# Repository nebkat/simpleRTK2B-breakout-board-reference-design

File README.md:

# ArduSimple simpleRTK2B Breakout Board

This repository contains KiCAD schematics and the PCB design for a breakout board for the simpleRTK2B.

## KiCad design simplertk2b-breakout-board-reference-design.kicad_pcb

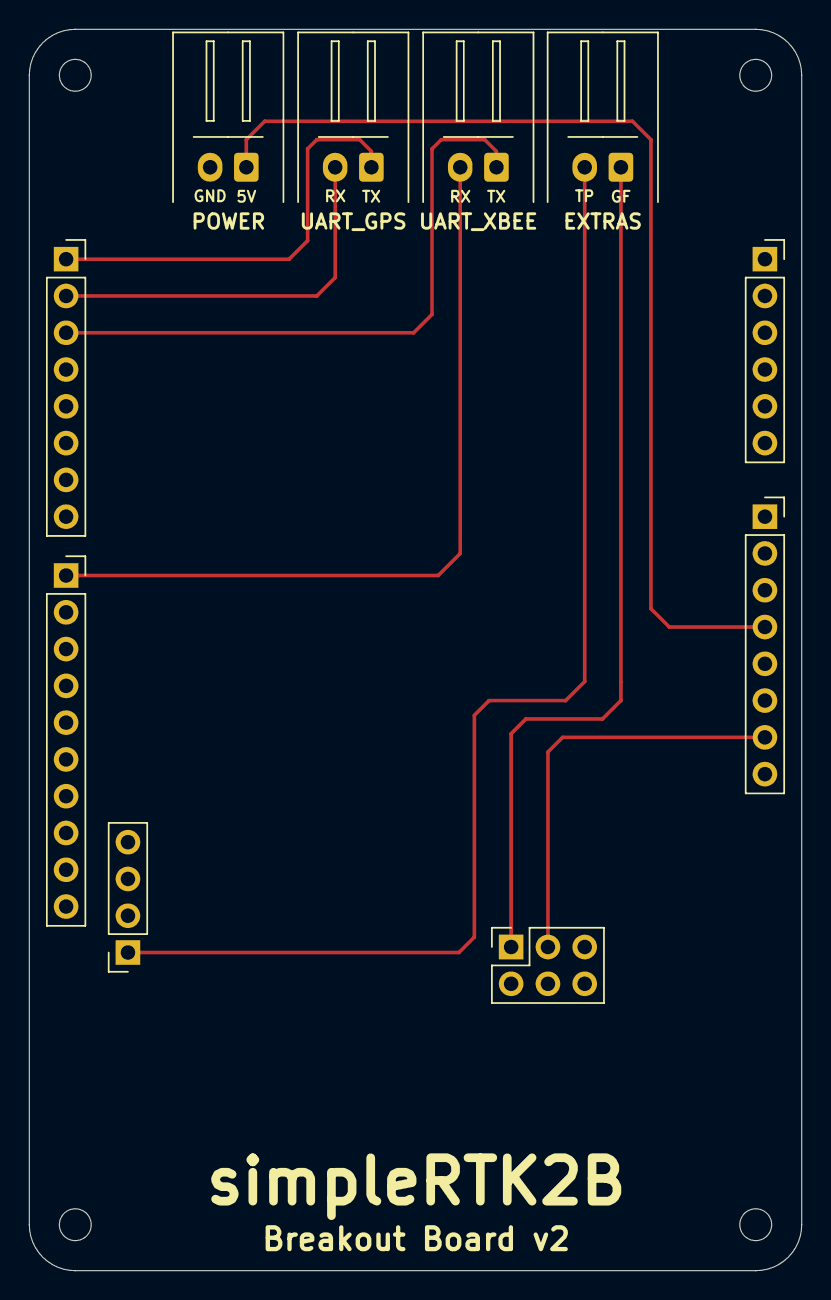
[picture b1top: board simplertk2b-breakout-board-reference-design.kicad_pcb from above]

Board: 2 copper layers, 53.3 x 85.7 mm, 14 parts (0 on the bottom side), 9 nets.

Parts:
H1, H2, H3, H4: MountingHole; MountingHole_2.2mm_M2
J1: Conn_SR2B_A; PinSocket_1x08_P2.54mm_Vertical
J2: Conn_SR2B_C; PinSocket_1x10_P2.54mm_Vertical
J3: Conn_UART_GPS; JST_XH_S02B-XH-A_1x02_P2.50mm_Horizontal
J4: Conn_UART_XBEE; JST_XH_S02B-XH-A_1x02_P2.50mm_Horizontal
J5: Conn_POWER; JST_XH_S02B-XH-A_1x02_P2.50mm_Horizontal
J6: Conn_Extra; JST_XH_S02B-XH-A_1x02_P2.50mm_Horizontal
J7: Conn_SR2B_E; PinSocket_1x04_P2.54mm_Vertical
J8: Conn_SR2B_F; PinSocket_2x03_P2.54mm_Vertical
J11: Conn_SR2B_B; PinSocket_1x06_P2.54mm_Vertical
J12: Conn_SR2B_D; PinSocket_1x08_P2.54mm_Vertical

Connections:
+3V3: J8.3, J12.7
+5V: J5.1, J12.4
GEOFENCE: J6.1, J8.1
GND: J2.7, J5.2, J8.4, J8.6, J12.2, J12.3
GPS_RX: J1.2, J3.2
GPS_TX: J1.1, J3.1
TIMEPULSE: J6.2, J7.1
XBEE_RX: J2.1, J4.2
XBEE_TX: J1.3, J4.1
